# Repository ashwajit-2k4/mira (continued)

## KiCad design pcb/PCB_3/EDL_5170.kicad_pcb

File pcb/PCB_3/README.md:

# TMAG5170 Sensor Array PCB

This PCB serves as a **backup** to the main TMAG3001-based board, utilizing **TMAG5170** sensors to form an 8×8 magnetometer array. It is a **2-layer** board designed for ease of hand assembly and SPI-based communication.

## Overview

- **Sensor Type**: TMAG5170 3-axis magnetometers  
- **Array Size**: 8×8 grid (64 sensors)  
- **Inter-sensor Spacing**: 4.625 mm  
- **PCB Type**: 2-layer board  
- **Communication Protocol**: SPI  

---

## Design Details

### SPI Bus Structure

Each **bus** handles 8 sensors (as seen in the schematic).  
- Required lines per bus: `INT`, `SCLK`, `MOSI`, `MISO`  
- Compatible with the same CMOD PCB interface used by the TMAG3001 board  
- Pins per TMAG5170 IC:
  - `VCC`, `GND`, `ALERT`, `SCLK`, `MOSI`, `MISO`, `TEST`, `CS`

> **Note**: Pin mapping ensures drop-in compatibility with existing CMOD interface hardware.

### Electrical Components

- **Pull-up Resistors**: 1.8 kΩ on all lines  
- **Decoupling Capacitors**:
  - 0.1 µF for each sensor IC  
  - 2 × 1 µF bulk capacitors at the input supply

### Physical Layout

- **IC Placement**: Only the TMAG5170 ICs are on the **front** of the PCB  
- **Other Components**: All resistors, capacitors, and connectors are on the **back**, minimizing interference during sensor operation   
- **Test Points**: 8 test points at the **bottom** of the PCB for signal and ground verification

### Assembly & Grounding

- Designed for **hand-soldering** – large enough component footprints  
- Both PCB layers are filled with **ground planes** for signal integrity

---

## Files & Resources

The repository folders include:
- **Schematic**
- **PCB Layout**
- **3D Renders**
- **Assembled PCB Images**

---

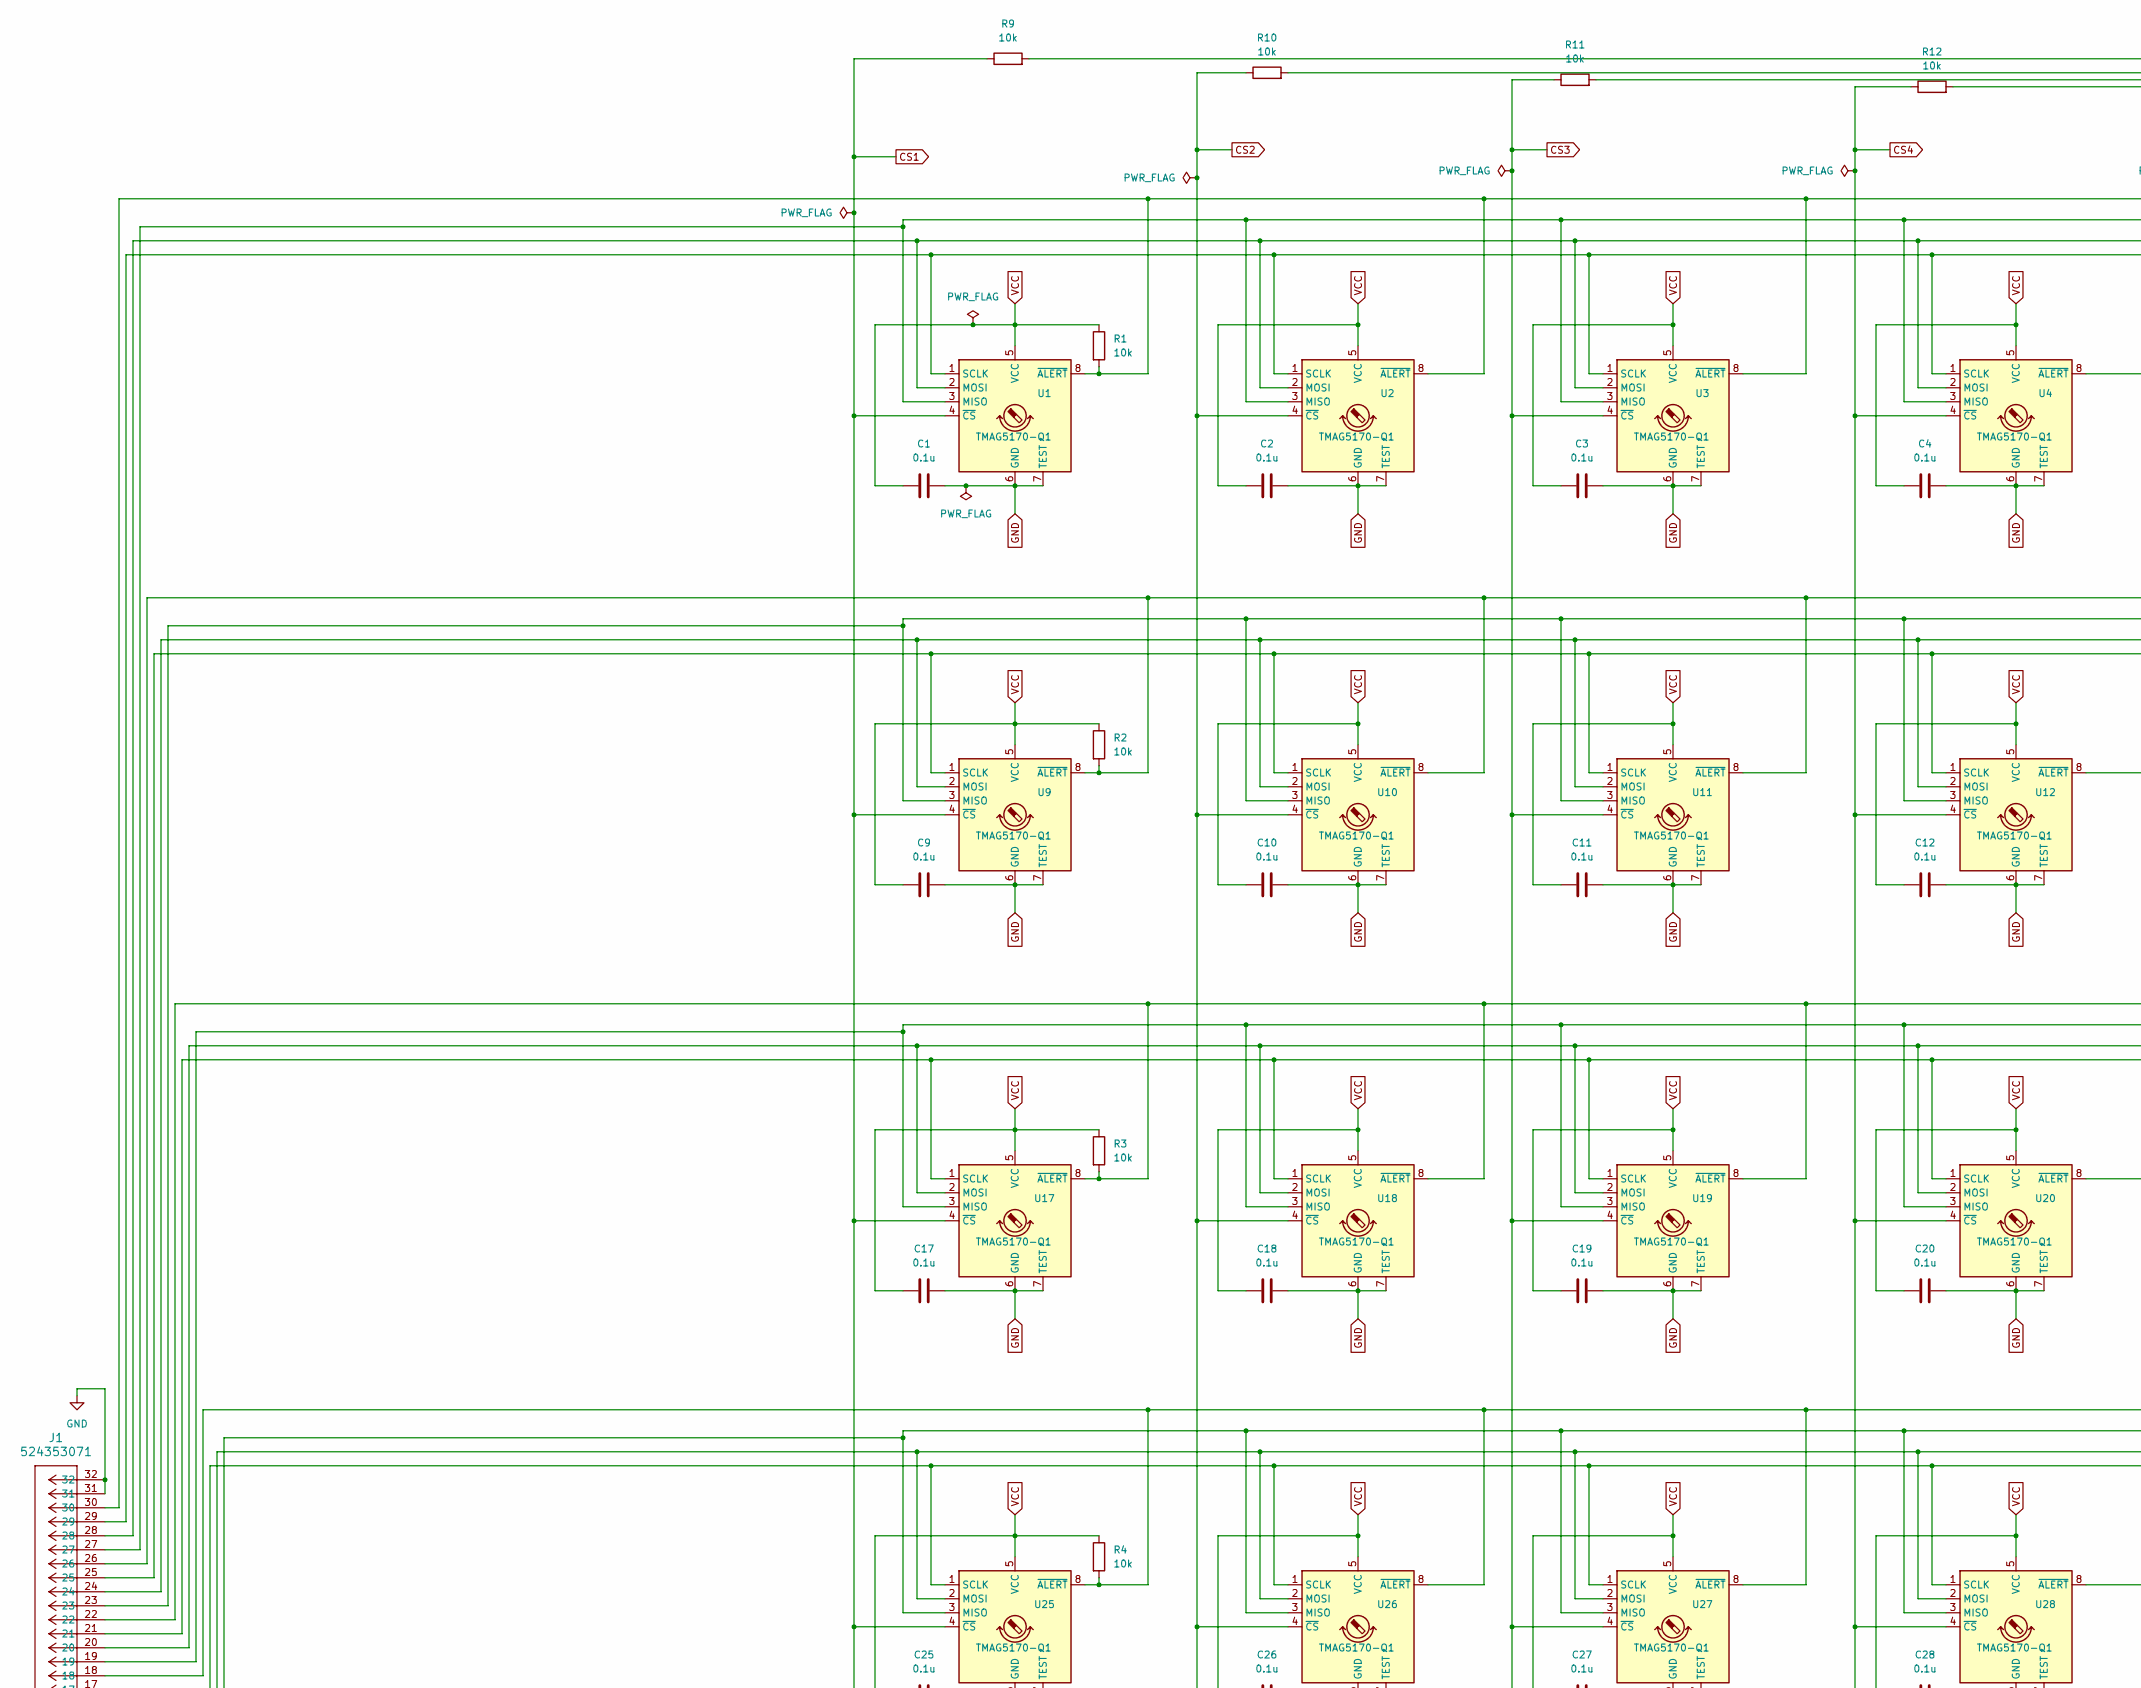
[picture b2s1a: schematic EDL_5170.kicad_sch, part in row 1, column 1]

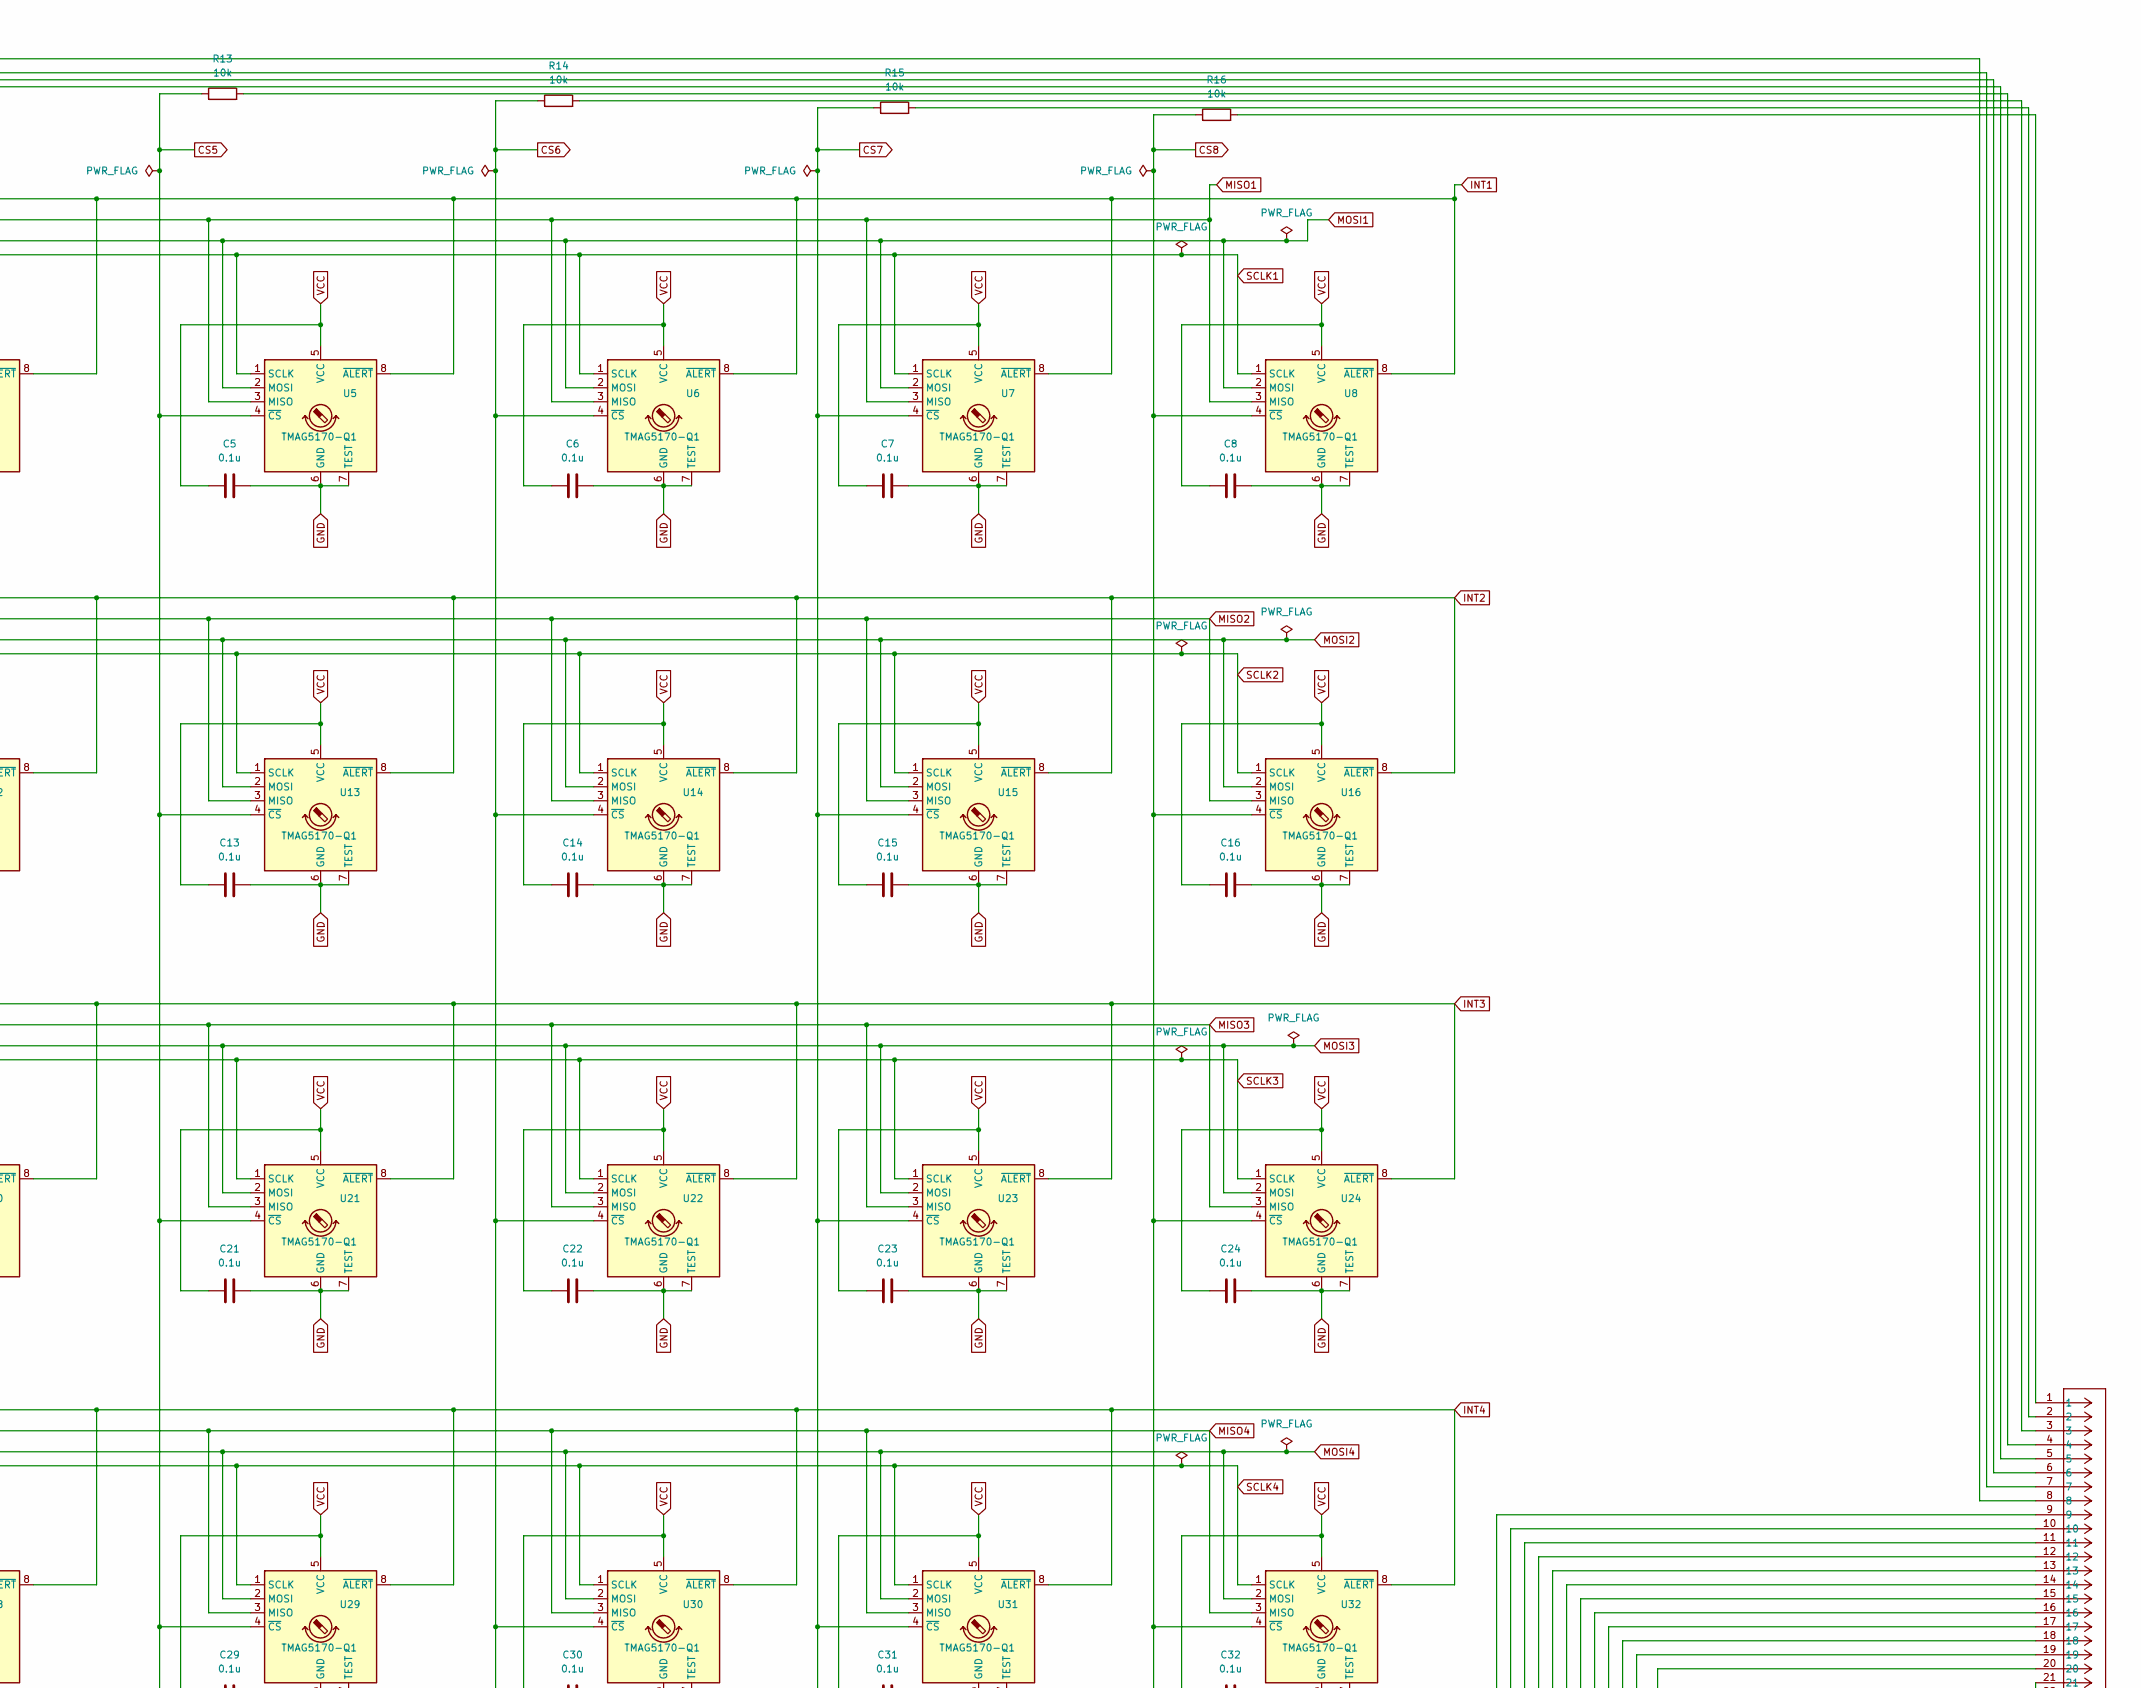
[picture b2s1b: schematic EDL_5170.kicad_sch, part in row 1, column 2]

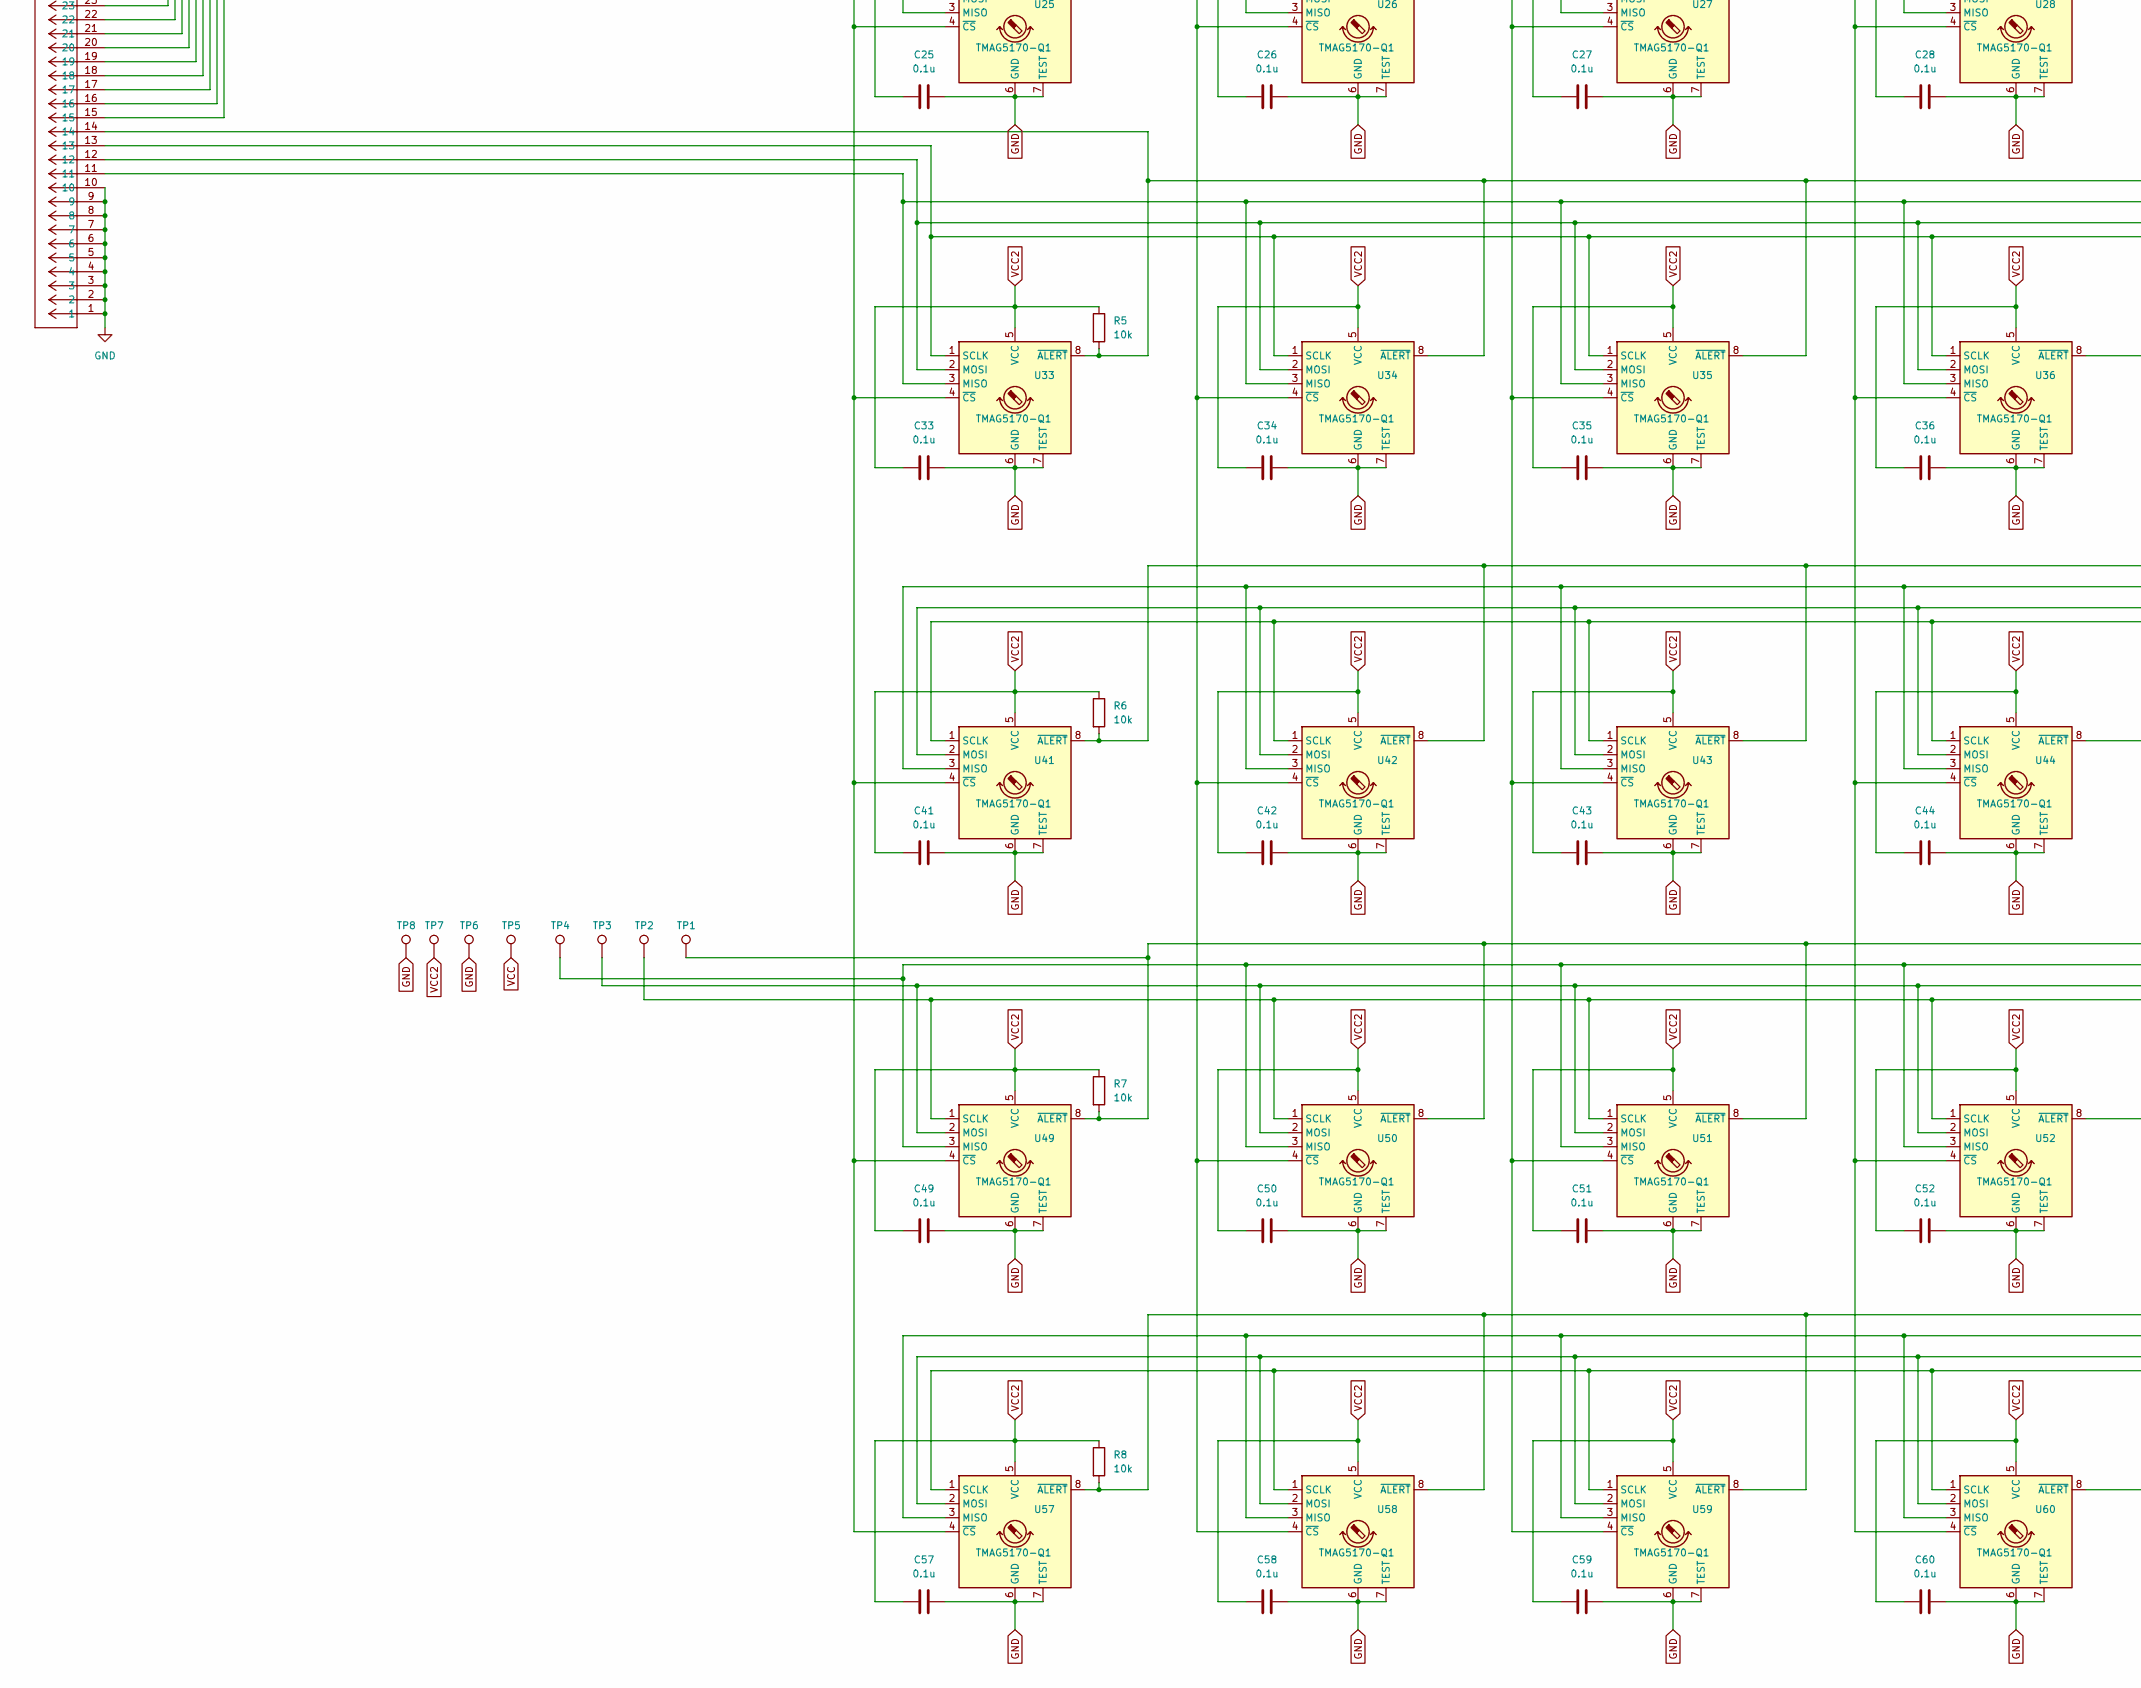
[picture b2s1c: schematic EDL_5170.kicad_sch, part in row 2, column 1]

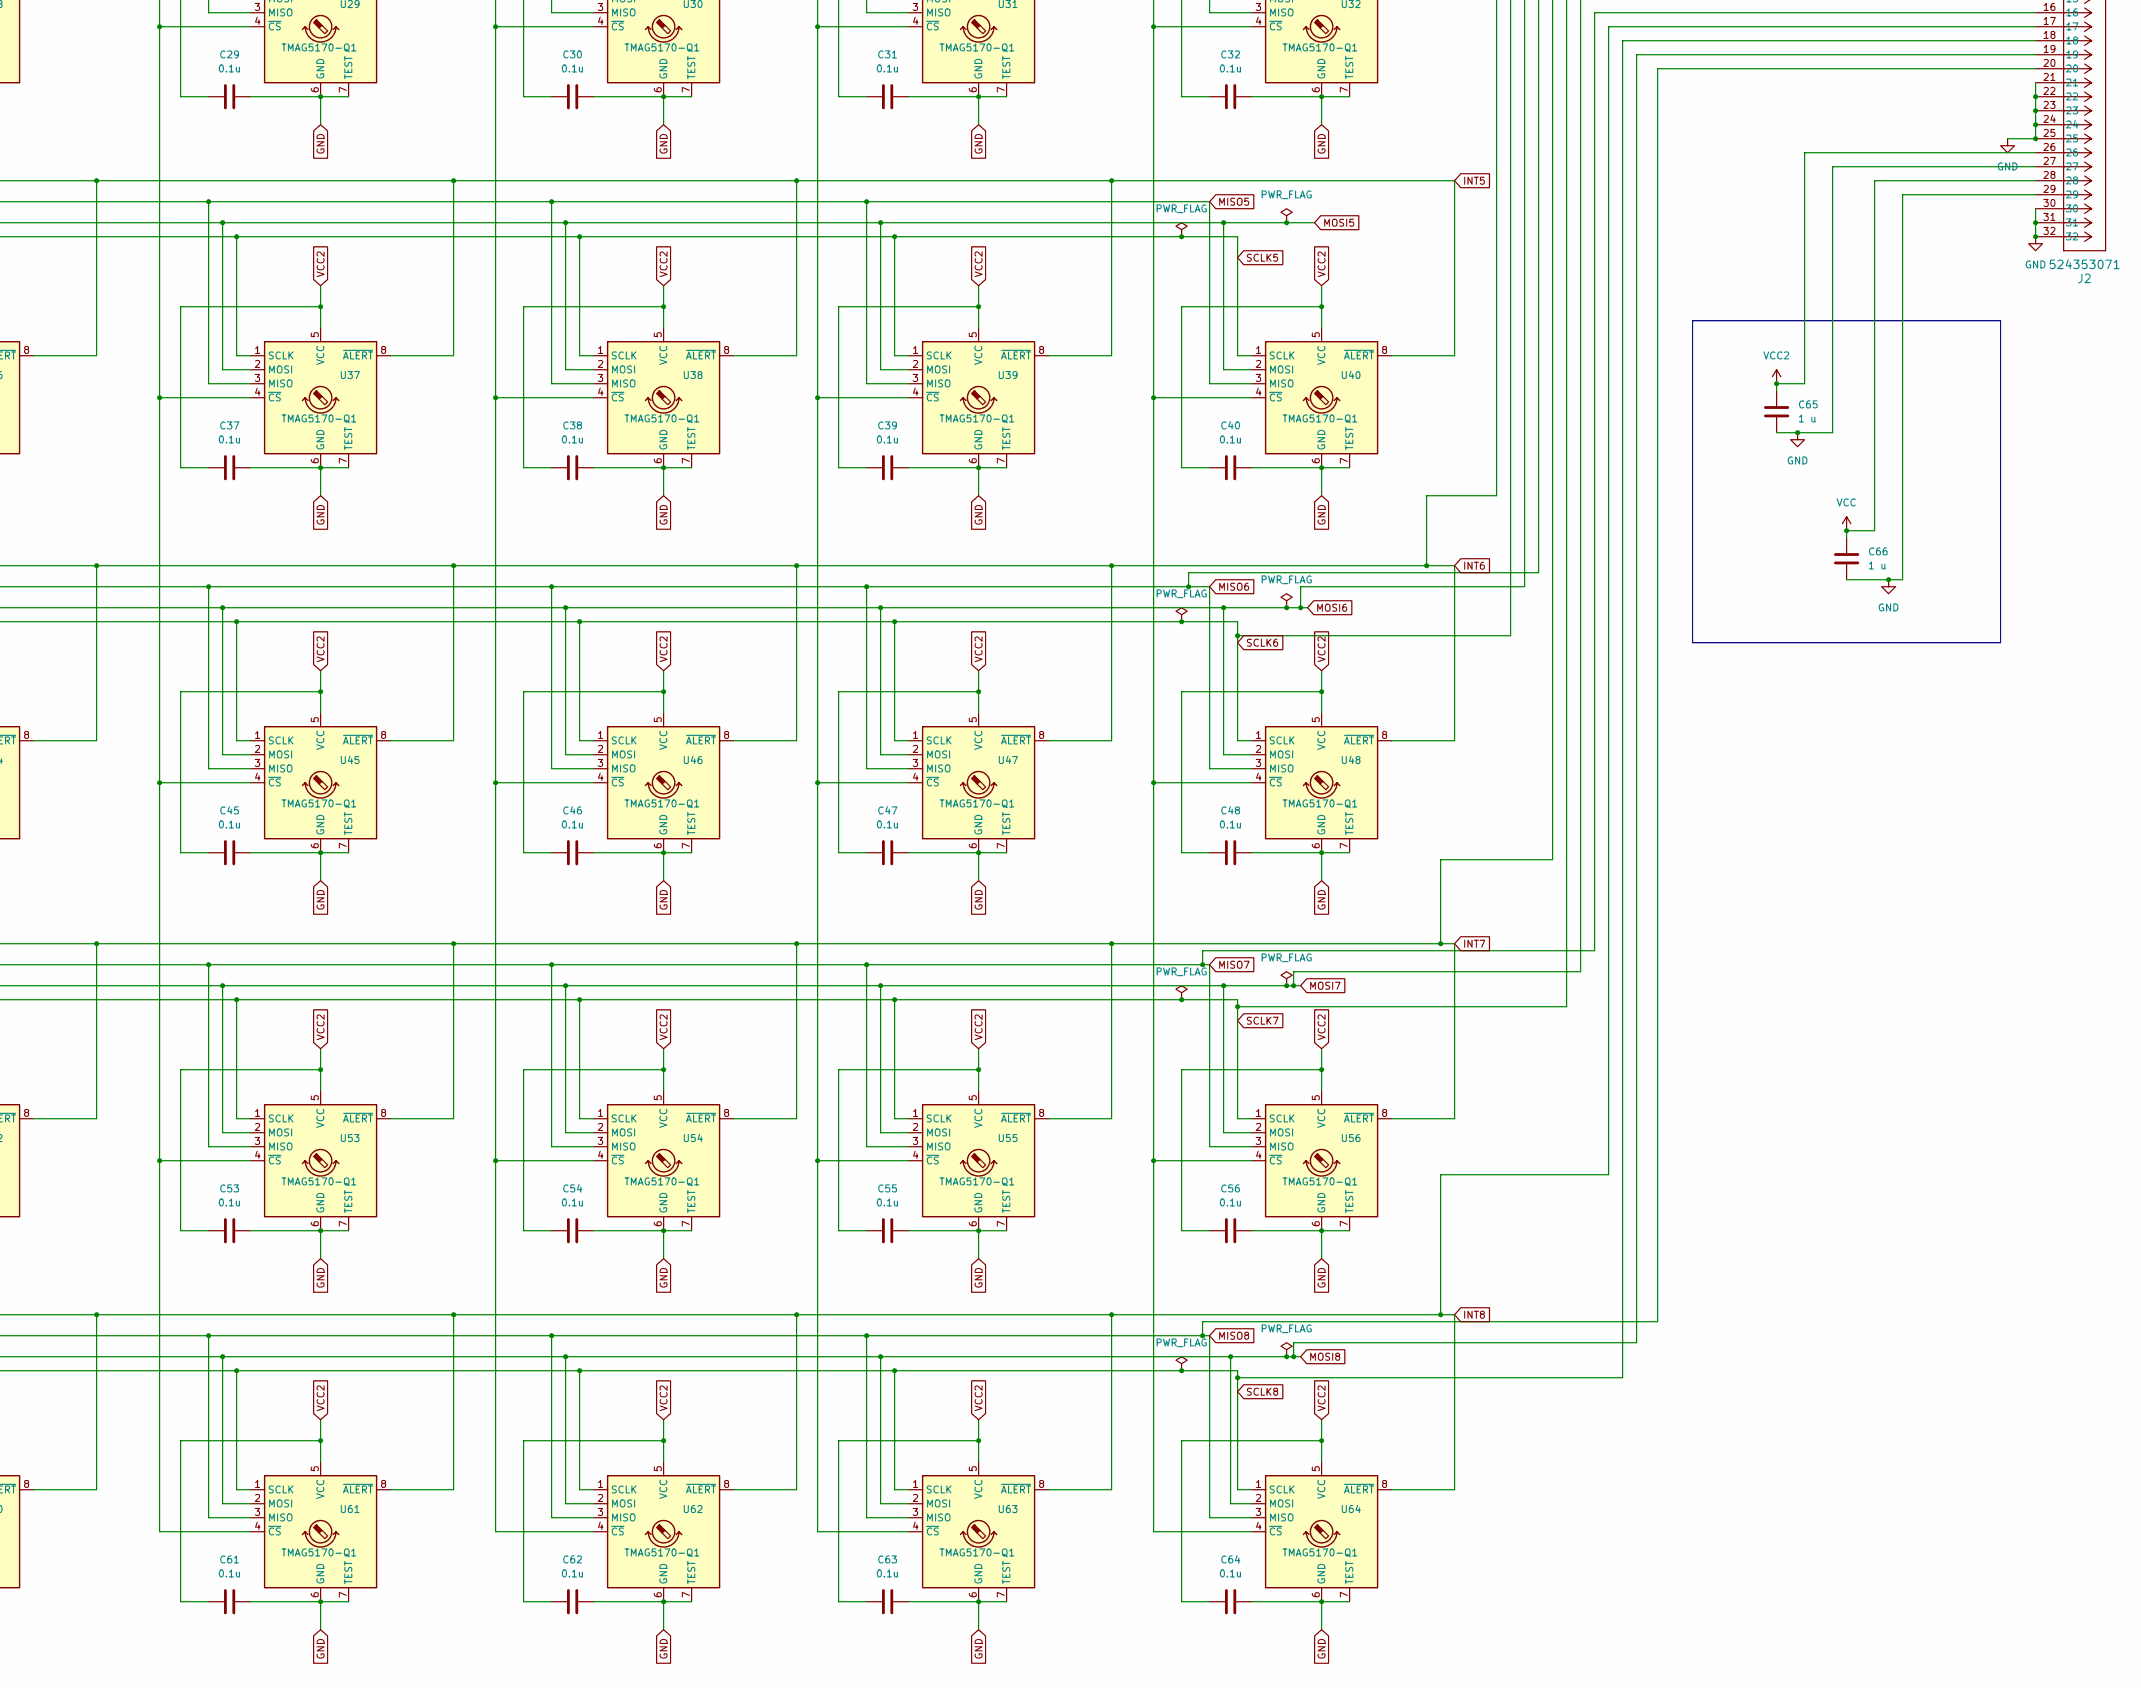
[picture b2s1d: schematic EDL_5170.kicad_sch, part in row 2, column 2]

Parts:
C1, C2, C3, C4, C5, C6, C7, C8, C9, C10, C11, C12, C13, C14, C15, C16, C17, C18, C19, C20, C21, C22, C23, C24, C25, C26, C27, C28, C29, C30, C31, C32, C33, C34, C35, C36, C37, C38, C39, C40, C41, C42, C43, C44, C45, C46, C47, C48, C49, C50, C51, C52, C53, C54, C55, C56, C57, C58, C59, C60, C61, C62, C63, C64: 0.1u; C_1206_3216Metric_Pad1.33x1.80mm_HandSolder
C65, C66: 1 u; C_1206_3216Metric
J1, J2: 524353071; 52435-3071
R1, R2, R3, R4, R5, R6, R7, R8, R9, R10, R11, R12, R13, R14, R15, R16: 10k; R_1206_3216Metric_Pad1.30x1.75mm_HandSolder
TP1, TP2, TP3, TP4, TP5, TP6, TP7, TP8: TestPoint; TestPoint_Plated_Hole_D2.0mm
U1, U2, U3, U4, U5, U6, U7, U8, U9, U10, U11, U12, U13, U14, U15, U16, U17, U18, U19, U20, U21, U22, U23, U24, U25, U26, U27, U28, U29, U30, U31, U32, U33, U34, U35, U36, U37, U38, U39, U40, U41, U42, U43, U44, U45, U46, U47, U48, U49, U50, U51, U52, U53, U54, U55, U56, U57, U58, U59, U60, U61, U62, U63, U64: TMAG5170-Q1; Texas_S-PDSO-G8_3x3mm_P0.65mm

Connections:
CS1: R9.1, U1.4 (~CS), U9.4 (~CS), U17.4 (~CS), U25.4 (~CS), U33.4 (~CS), U41.4 (~CS), U49.4 (~CS), U57.4 (~CS)
CS2: R10.1, U2.4 (~CS), U10.4 (~CS), U18.4 (~CS), U26.4 (~CS), U34.4 (~CS), U42.4 (~CS), U50.4 (~CS), U58.4 (~CS)
CS3: R11.1, U3.4 (~CS), U11.4 (~CS), U19.4 (~CS), U27.4 (~CS), U35.4 (~CS), U43.4 (~CS), U51.4 (~CS), U59.4 (~CS)
CS4: R12.1, U4.4 (~CS), U12.4 (~CS), U20.4 (~CS), U28.4 (~CS), U36.4 (~CS), U44.4 (~CS), U52.4 (~CS), U60.4 (~CS)
CS5: R13.1, U5.4 (~CS), U13.4 (~CS), U21.4 (~CS), U29.4 (~CS), U37.4 (~CS), U45.4 (~CS), U53.4 (~CS), U61.4 (~CS)
CS6: R14.1, U6.4 (~CS), U14.4 (~CS), U22.4 (~CS), U30.4 (~CS), U38.4 (~CS), U46.4 (~CS), U54.4 (~CS), U62.4 (~CS)
CS7: R15.1, U7.4 (~CS), U15.4 (~CS), U23.4 (~CS), U31.4 (~CS), U39.4 (~CS), U47.4 (~CS), U55.4 (~CS), U63.4 (~CS)
CS8: R16.1, U8.4 (~CS), U16.4 (~CS), U24.4 (~CS), U32.4 (~CS), U40.4 (~CS), U48.4 (~CS), U56.4 (~CS), U64.4 (~CS)
GND: C1.2, C2.2, C3.2, C4.2, C5.2, C6.2, C7.2, C8.2, C9.2, C10.2, C11.2, C12.2, C13.2, C14.2, C15.2, C16.2, C17.2, C18.2, C19.2, C20.2, C21.2, C22.2, C23.2, C24.2, C25.2, C26.2, C27.2, C28.2, C29.2, C30.2, C31.2, C32.2, C33.2, C34.2, C35.2, C36.2, C37.2, C38.2, C39.2, C40.2, C41.2, C42.2, C43.2, C44.2, C45.2, C46.2, C47.2, C48.2, C49.2, C50.2, C51.2, C52.2, C53.2, C54.2, C55.2, C56.2, C57.2, C58.2, C59.2, C60.2, C61.2, C62.2, C63.2, C64.2, C65.2, C66.2, J1.1, J1.2, J1.3, J1.4, J1.5, J1.6, J1.7, J1.8, J1.9, J1.10, J1.31, J1.32, J2.21, J2.22, J2.23, J2.24, J2.25, J2.27, J2.29, J2.30, J2.31, J2.32, TP6.1, TP8.1, U1.6 (GND), U1.7 (TEST), U2.6 (GND), U2.7 (TEST), U3.6 (GND), U3.7 (TEST), U4.6 (GND), U4.7 (TEST), U5.6 (GND), U5.7 (TEST), U6.6 (GND), U6.7 (TEST), U7.6 (GND), U7.7 (TEST), U8.6 (GND), U8.7 (TEST), U9.6 (GND), U9.7 (TEST), U10.6 (GND), U10.7 (TEST), U11.6 (GND), U11.7 (TEST), U12.6 (GND), U12.7 (TEST), U13.6 (GND), U13.7 (TEST), U14.6 (GND), U14.7 (TEST), U15.6 (GND), U15.7 (TEST), U16.6 (GND), U16.7 (TEST), U17.6 (GND), U17.7 (TEST), U18.6 (GND), U18.7 (TEST), U19.6 (GND), U19.7 (TEST), U20.6 (GND), U20.7 (TEST), U21.6 (GND), U21.7 (TEST), U22.6 (GND), U22.7 (TEST), U23.6 (GND), U23.7 (TEST), U24.6 (GND), U24.7 (TEST), U25.6 (GND), U25.7 (TEST), U26.6 (GND), U26.7 (TEST), U27.6 (GND), U27.7 (TEST), U28.6 (GND), U28.7 (TEST), U29.6 (GND), U29.7 (TEST), U30.6 (GND), U30.7 (TEST), U31.6 (GND), U31.7 (TEST), U32.6 (GND), U32.7 (TEST), U33.6 (GND), U33.7 (TEST), U34.6 (GND), U34.7 (TEST), U35.6 (GND), U35.7 (TEST), U36.6 (GND), U36.7 (TEST), U37.6 (GND), U37.7 (TEST), U38.6 (GND), U38.7 (TEST), U39.6 (GND), U39.7 (TEST), U40.6 (GND), U40.7 (TEST), U41.6 (GND), U41.7 (TEST), U42.6 (GND), U42.7 (TEST), U43.6 (GND), U43.7 (TEST), U44.6 (GND), U44.7 (TEST), U45.6 (GND), U45.7 (TEST), U46.6 (GND), U46.7 (TEST), U47.6 (GND), U47.7 (TEST), U48.6 (GND), U48.7 (TEST), U49.6 (GND), U49.7 (TEST), U50.6 (GND), U50.7 (TEST), U51.6 (GND), U51.7 (TEST), U52.6 (GND), U52.7 (TEST), U53.6 (GND), U53.7 (TEST), U54.6 (GND), U54.7 (TEST), U55.6 (GND), U55.7 (TEST), U56.6 (GND), U56.7 (TEST), U57.6 (GND), U57.7 (TEST), U58.6 (GND), U58.7 (TEST), U59.6 (GND), U59.7 (TEST), U60.6 (GND), U60.7 (TEST), U61.6 (GND), U61.7 (TEST), U62.6 (GND), U62.7 (TEST), U63.6 (GND), U63.7 (TEST), U64.6 (GND), U64.7 (TEST)
INT1: J1.30, R1.2, U1.8 (~ALERT), U2.8 (~ALERT), U3.8 (~ALERT), U4.8 (~ALERT), U5.8 (~ALERT), U6.8 (~ALERT), U7.8 (~ALERT), U8.8 (~ALERT)
INT2: J1.26, R2.2, U9.8 (~ALERT), U10.8 (~ALERT), U11.8 (~ALERT), U12.8 (~ALERT), U13.8 (~ALERT), U14.8 (~ALERT), U15.8 (~ALERT), U16.8 (~ALERT)
INT3: J1.22, R3.2, U17.8 (~ALERT), U18.8 (~ALERT), U19.8 (~ALERT), U20.8 (~ALERT), U21.8 (~ALERT), U22.8 (~ALERT), U23.8 (~ALERT), U24.8 (~ALERT)
INT4: J1.18, R4.2, U25.8 (~ALERT), U26.8 (~ALERT), U27.8 (~ALERT), U28.8 (~ALERT), U29.8 (~ALERT), U30.8 (~ALERT), U31.8 (~ALERT), U32.8 (~ALERT)
INT5: J1.14, R5.2, U33.8 (~ALERT), U34.8 (~ALERT), U35.8 (~ALERT), U36.8 (~ALERT), U37.8 (~ALERT), U38.8 (~ALERT), U39.8 (~ALERT), U40.8 (~ALERT)
INT6: J2.9, R6.2, U41.8 (~ALERT), U42.8 (~ALERT), U43.8 (~ALERT), U44.8 (~ALERT), U45.8 (~ALERT), U46.8 (~ALERT), U47.8 (~ALERT), U48.8 (~ALERT)
INT7: J2.13, R7.2, TP1.1, U49.8 (~ALERT), U50.8 (~ALERT), U51.8 (~ALERT), U52.8 (~ALERT), U53.8 (~ALERT), U54.8 (~ALERT), U55.8 (~ALERT), U56.8 (~ALERT)
INT8: J2.17, R8.2, U57.8 (~ALERT), U58.8 (~ALERT), U59.8 (~ALERT), U60.8 (~ALERT), U61.8 (~ALERT), U62.8 (~ALERT), U63.8 (~ALERT), U64.8 (~ALERT)
MISO1: J1.27, U1.3 (MISO), U2.3 (MISO), U3.3 (MISO), U4.3 (MISO), U5.3 (MISO), U6.3 (MISO), U7.3 (MISO), U8.3 (MISO)
MISO2: J1.23, U9.3 (MISO), U10.3 (MISO), U11.3 (MISO), U12.3 (MISO), U13.3 (MISO), U14.3 (MISO), U15.3 (MISO), U16.3 (MISO)
MISO3: J1.19, U17.3 (MISO), U18.3 (MISO), U19.3 (MISO), U20.3 (MISO), U21.3 (MISO), U22.3 (MISO), U23.3 (MISO), U24.3 (MISO)
MISO4: J1.15, U25.3 (MISO), U26.3 (MISO), U27.3 (MISO), U28.3 (MISO), U29.3 (MISO), U30.3 (MISO), U31.3 (MISO), U32.3 (MISO)
MISO5: J1.11, U33.3 (MISO), U34.3 (MISO), U35.3 (MISO), U36.3 (MISO), U37.3 (MISO), U38.3 (MISO), U39.3 (MISO), U40.3 (MISO)
MISO6: J2.12, U41.3 (MISO), U42.3 (MISO), U43.3 (MISO), U44.3 (MISO), U45.3 (MISO), U46.3 (MISO), U47.3 (MISO), U48.3 (MISO)
MISO7: J2.16, TP4.1, U49.3 (MISO), U50.3 (MISO), U51.3 (MISO), U52.3 (MISO), U53.3 (MISO), U54.3 (MISO), U55.3 (MISO), U56.3 (MISO)
MISO8: J2.20, U57.3 (MISO), U58.3 (MISO), U59.3 (MISO), U60.3 (MISO), U61.3 (MISO), U62.3 (MISO), U63.3 (MISO), U64.3 (MISO)
MOSI1: J1.28, U1.2 (MOSI), U2.2 (MOSI), U3.2 (MOSI), U4.2 (MOSI), U5.2 (MOSI), U6.2 (MOSI), U7.2 (MOSI), U8.2 (MOSI)
MOSI2: J1.24, U9.2 (MOSI), U10.2 (MOSI), U11.2 (MOSI), U12.2 (MOSI), U13.2 (MOSI), U14.2 (MOSI), U15.2 (MOSI), U16.2 (MOSI)
MOSI3: J1.20, U17.2 (MOSI), U18.2 (MOSI), U19.2 (MOSI), U20.2 (MOSI), U21.2 (MOSI), U22.2 (MOSI), U23.2 (MOSI), U24.2 (MOSI)
MOSI4: J1.16, U25.2 (MOSI), U26.2 (MOSI), U27.2 (MOSI), U28.2 (MOSI), U29.2 (MOSI), U30.2 (MOSI), U31.2 (MOSI), U32.2 (MOSI)
MOSI5: J1.12, U33.2 (MOSI), U34.2 (MOSI), U35.2 (MOSI), U36.2 (MOSI), U37.2 (MOSI), U38.2 (MOSI), U39.2 (MOSI), U40.2 (MOSI)
MOSI6: J2.11, U41.2 (MOSI), U42.2 (MOSI), U43.2 (MOSI), U44.2 (MOSI), U45.2 (MOSI), U46.2 (MOSI), U47.2 (MOSI), U48.2 (MOSI)
MOSI7: J2.15, TP3.1, U49.2 (MOSI), U50.2 (MOSI), U51.2 (MOSI), U52.2 (MOSI), U53.2 (MOSI), U54.2 (MOSI), U55.2 (MOSI), U56.2 (MOSI)
MOSI8: J2.19, U57.2 (MOSI), U58.2 (MOSI), U59.2 (MOSI), U60.2 (MOSI), U61.2 (MOSI), U62.2 (MOSI), U63.2 (MOSI), U64.2 (MOSI)
unnamed: J2.1, R16.2
unnamed: J2.2, R15.2
unnamed: J2.3, R14.2
unnamed: J2.4, R13.2
unnamed: J2.5, R12.2
unnamed: J2.6, R11.2
unnamed: J2.7, R10.2
unnamed: J2.8, R9.2
SCLK1: J1.29, U1.1 (SCLK), U2.1 (SCLK), U3.1 (SCLK), U4.1 (SCLK), U5.1 (SCLK), U6.1 (SCLK), U7.1 (SCLK), U8.1 (SCLK)
SCLK2: J1.25, U9.1 (SCLK), U10.1 (SCLK), U11.1 (SCLK), U12.1 (SCLK), U13.1 (SCLK), U14.1 (SCLK), U15.1 (SCLK), U16.1 (SCLK)
SCLK3: J1.21, U17.1 (SCLK), U18.1 (SCLK), U19.1 (SCLK), U20.1 (SCLK), U21.1 (SCLK), U22.1 (SCLK), U23.1 (SCLK), U24.1 (SCLK)
SCLK4: J1.17, U25.1 (SCLK), U26.1 (SCLK), U27.1 (SCLK), U28.1 (SCLK), U29.1 (SCLK), U30.1 (SCLK), U31.1 (SCLK), U32.1 (SCLK)
SCLK5: J1.13, U33.1 (SCLK), U34.1 (SCLK), U35.1 (SCLK), U36.1 (SCLK), U37.1 (SCLK), U38.1 (SCLK), U39.1 (SCLK), U40.1 (SCLK)
SCLK6: J2.10, U41.1 (SCLK), U42.1 (SCLK), U43.1 (SCLK), U44.1 (SCLK), U45.1 (SCLK), U46.1 (SCLK), U47.1 (SCLK), U48.1 (SCLK)
SCLK7: J2.14, TP2.1, U49.1 (SCLK), U50.1 (SCLK), U51.1 (SCLK), U52.1 (SCLK), U53.1 (SCLK), U54.1 (SCLK), U55.1 (SCLK), U56.1 (SCLK)
SCLK8: J2.18, U57.1 (SCLK), U58.1 (SCLK), U59.1 (SCLK), U60.1 (SCLK), U61.1 (SCLK), U62.1 (SCLK), U63.1 (SCLK), U64.1 (SCLK)
VCC: C1.1, C2.1, C3.1, C4.1, C5.1, C6.1, C7.1, C8.1, C9.1, C10.1, C11.1, C12.1, C13.1, C14.1, C15.1, C16.1, C17.1, C18.1, C19.1, C20.1, C21.1, C22.1, C23.1, C24.1, C25.1, C26.1, C27.1, C28.1, C29.1, C30.1, C31.1, C32.1, C66.1, J2.28, R1.1, R2.1, R3.1, R4.1, TP5.1, U1.5 (VCC), U2.5 (VCC), U3.5 (VCC), U4.5 (VCC), U5.5 (VCC), U6.5 (VCC), U7.5 (VCC), U8.5 (VCC), U9.5 (VCC), U10.5 (VCC), U11.5 (VCC), U12.5 (VCC), U13.5 (VCC), U14.5 (VCC), U15.5 (VCC), U16.5 (VCC), U17.5 (VCC), U18.5 (VCC), U19.5 (VCC), U20.5 (VCC), U21.5 (VCC), U22.5 (VCC), U23.5 (VCC), U24.5 (VCC), U25.5 (VCC), U26.5 (VCC), U27.5 (VCC), U28.5 (VCC), U29.5 (VCC), U30.5 (VCC), U31.5 (VCC), U32.5 (VCC)
VCC2: C33.1, C34.1, C35.1, C36.1, C37.1, C38.1, C39.1, C40.1, C41.1, C42.1, C43.1, C44.1, C45.1, C46.1, C47.1, C48.1, C49.1, C50.1, C51.1, C52.1, C53.1, C54.1, C55.1, C56.1, C57.1, C58.1, C59.1, C60.1, C61.1, C62.1, C63.1, C64.1, C65.1, J2.26, R5.1, R6.1, R7.1, R8.1, TP7.1, U33.5 (VCC), U34.5 (VCC), U35.5 (VCC), U36.5 (VCC), U37.5 (VCC), U38.5 (VCC), U39.5 (VCC), U40.5 (VCC), U41.5 (VCC), U42.5 (VCC), U43.5 (VCC), U44.5 (VCC), U45.5 (VCC), U46.5 (VCC), U47.5 (VCC), U48.5 (VCC), U49.5 (VCC), U50.5 (VCC), U51.5 (VCC), U52.5 (VCC), U53.5 (VCC), U54.5 (VCC), U55.5 (VCC), U56.5 (VCC), U57.5 (VCC), U58.5 (VCC), U59.5 (VCC), U60.5 (VCC), U61.5 (VCC), U62.5 (VCC), U63.5 (VCC), U64.5 (VCC)
